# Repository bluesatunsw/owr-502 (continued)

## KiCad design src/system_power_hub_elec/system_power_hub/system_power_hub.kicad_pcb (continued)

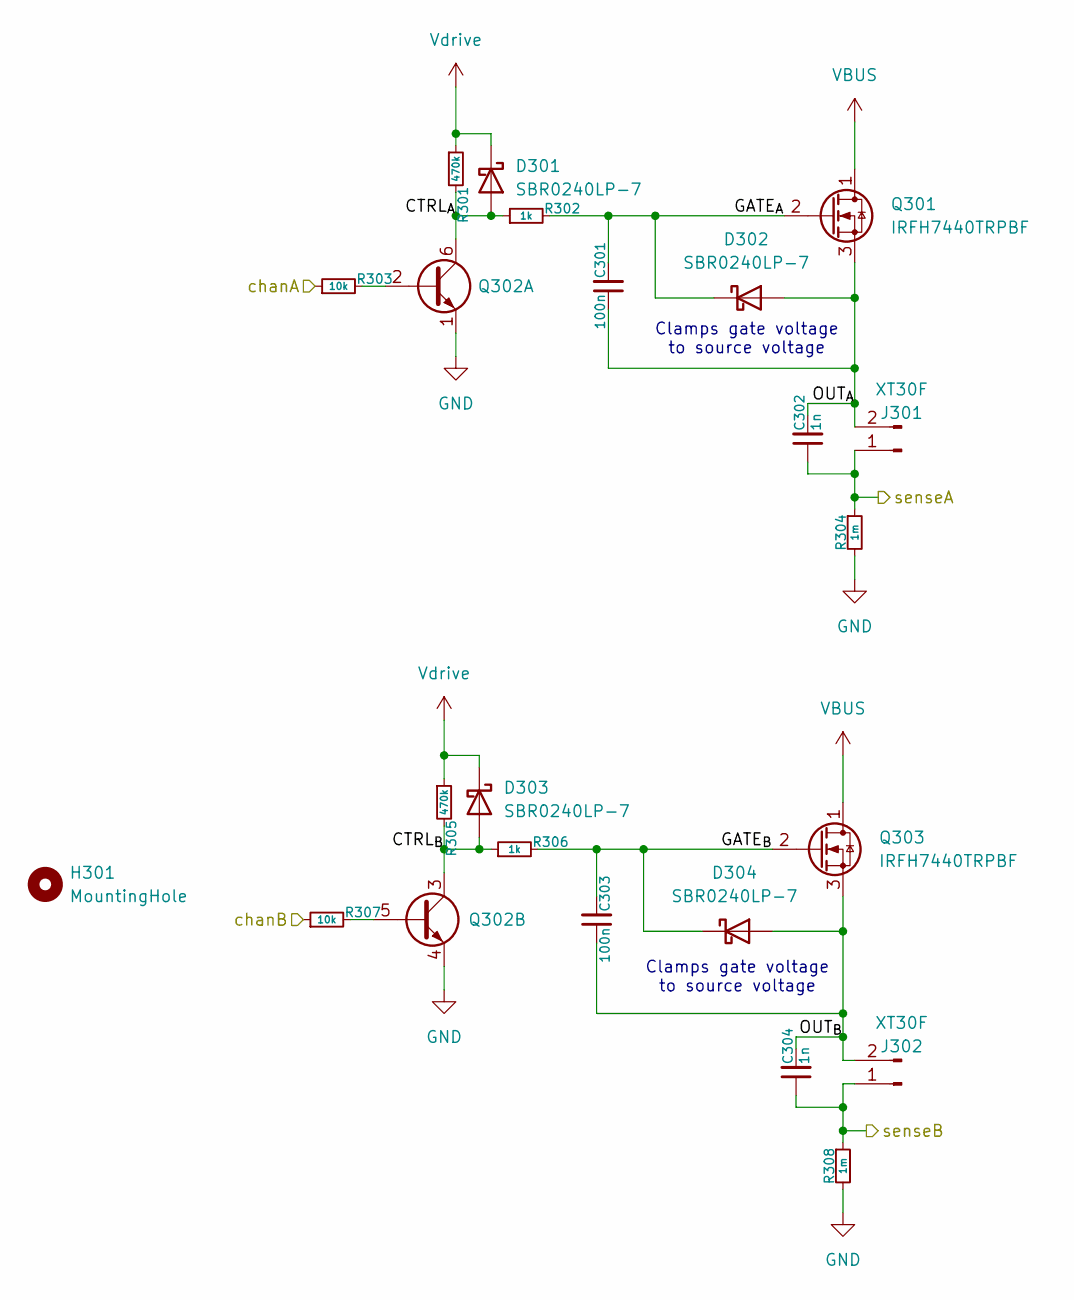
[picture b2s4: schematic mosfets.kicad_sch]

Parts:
C301, C303: 100n; C_0402_1005Metric
C302, C304: 1n; C_0402_1005Metric
D301, D302, D303, D304: SBR0240LP-7; D_SOD-882
H301: MountingHole; M2.5_Internal
J301, J302: XT30F; AMASS_XT30PW-F_1x02_P2.50mm_Horizontal
Q301, Q303: IRFH7440TRPBF; PQFN_5x6mm_E_DGS
Q302: Q_Dual_NPN_NPN_E1B1C2E2B2C1; SOT-363
R301, R305: 470k; R_0402_1005Metric
R302, R306: 1k; R_0402_1005Metric
R303, R307: 10k; R_0402_1005Metric
R304, R308: 1m; R_2512_6332Metric

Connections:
/Analog Stuff/Mosfets 1/CTRL_{A}: D301.2 (A), Q302.6 (C1), R301.2, R302.1
/Analog Stuff/Mosfets 1/CTRL_{B}: D303.2 (A), Q302.3 (C2), R305.2, R306.1
/Analog Stuff/Mosfets 1/GATE_{A}: C301.2, D302.1 (K), Q301.2 (G), R302.2
/Analog Stuff/Mosfets 1/GATE_{B}: C303.2, D304.1 (K), Q303.2 (G), R306.2
/Analog Stuff/Mosfets 1/OUT_{A}: C301.1, C302.2, D302.2 (A), J301.2, Q301.3 (S)
/Analog Stuff/Mosfets 1/OUT_{B}: C303.1, C304.2, D304.2 (A), J302.2, Q303.3 (S)
/Analog Stuff/vsense_p2: C302.1, J301.1, R304.1; also elsewhere on the board
/Analog Stuff/vsense_p3: C304.1, J302.1, R308.1; also elsewhere on the board
/Analog Stuff/~chan2: R303.1; also elsewhere on the board
/Analog Stuff/~chan3: R307.1; also elsewhere on the board
GND: Q302.1 (E1), Q302.4 (E2), R304.2, R308.2; also elsewhere on the board
unnamed: Q302.2 (B1), R303.2
unnamed: Q302.5 (B2), R307.2
VBUS: Q301.1 (D), Q303.1 (D); also elsewhere on the board
Vdrive: D301.1 (K), D303.1 (K), R301.1, R305.1; also elsewhere on the board

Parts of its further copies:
C401, C403, C501, C503, C601, C603: 100n; C_0402_1005Metric
C402, C404, C502, C504, C602, C604: 1n; C_0402_1005Metric
D401, D402, D403, D404, D501, D502, D503, D504, D601, D602, D603, D604: SBR0240LP-7; D_SOD-882
H401, H501, H601: MountingHole; M2.5_Internal
J401, J402, J501, J502, J601, J602: XT30F; AMASS_XT30PW-F_1x02_P2.50mm_Horizontal
Q401, Q403, Q501, Q503, Q601, Q603: IRFH7440TRPBF; PQFN_5x6mm_E_DGS
Q402, Q502, Q602: Q_Dual_NPN_NPN_E1B1C2E2B2C1; SOT-363
R401, R405, R501, R505, R601, R605: 470k; R_0402_1005Metric
R402, R406, R502, R506, R602, R606: 1k; R_0402_1005Metric
R403, R407, R503, R507, R603, R607: 10k; R_0402_1005Metric
R404, R408, R504, R508, R604, R608: 1m; R_2512_6332Metric

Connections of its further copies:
/Analog Stuff/Mosfets 2/CTRL_{A}: D401.2 (A), Q402.6 (C1), R401.2, R402.1
/Analog Stuff/Mosfets 2/CTRL_{B}: D403.2 (A), Q402.3 (C2), R405.2, R406.1
/Analog Stuff/Mosfets 2/GATE_{A}: C401.2, D402.1 (K), Q401.2 (G), R402.2
/Analog Stuff/Mosfets 2/GATE_{B}: C403.2, D404.1 (K), Q403.2 (G), R406.2
/Analog Stuff/Mosfets 2/OUT_{A}: C401.1, C402.2, D402.2 (A), J401.2, Q401.3 (S)
/Analog Stuff/Mosfets 2/OUT_{B}: C403.1, C404.2, D404.2 (A), J402.2, Q403.3 (S)
/Analog Stuff/Mosfets 3/CTRL_{A}: D501.2 (A), Q502.6 (C1), R501.2, R502.1
/Analog Stuff/Mosfets 3/CTRL_{B}: D503.2 (A), Q502.3 (C2), R505.2, R506.1
/Analog Stuff/Mosfets 3/GATE_{A}: C501.2, D502.1 (K), Q501.2 (G), R502.2
/Analog Stuff/Mosfets 3/GATE_{B}: C503.2, D504.1 (K), Q503.2 (G), R506.2
/Analog Stuff/Mosfets 3/OUT_{A}: C501.1, C502.2, D502.2 (A), J501.2, Q501.3 (S)
/Analog Stuff/Mosfets 3/OUT_{B}: C503.1, C504.2, D504.2 (A), J502.2, Q503.3 (S)
/Analog Stuff/Mosfets 4/CTRL_{A}: D601.2 (A), Q602.6 (C1), R601.2, R602.1
/Analog Stuff/Mosfets 4/CTRL_{B}: D603.2 (A), Q602.3 (C2), R605.2, R606.1
/Analog Stuff/Mosfets 4/GATE_{A}: C601.2, D602.1 (K), Q601.2 (G), R602.2
/Analog Stuff/Mosfets 4/GATE_{B}: C603.2, D604.1 (K), Q603.2 (G), R606.2
/Analog Stuff/Mosfets 4/OUT_{A}: C601.1, C602.2, D602.2 (A), J601.2, Q601.3 (S)
/Analog Stuff/Mosfets 4/OUT_{B}: C603.1, C604.2, D604.2 (A), J602.2, Q603.3 (S)
/Analog Stuff/vsense_p0: C402.1, J401.1, R404.1; also elsewhere on the board
/Analog Stuff/vsense_p1: C404.1, J402.1, R408.1; also elsewhere on the board
/Analog Stuff/vsense_p4: C502.1, J501.1, R504.1; also elsewhere on the board
/Analog Stuff/vsense_p5: C504.1, J502.1, R508.1; also elsewhere on the board
/Analog Stuff/vsense_p6: C602.1, J601.1, R604.1; also elsewhere on the board
/Analog Stuff/vsense_p7: C604.1, J602.1, R608.1; also elsewhere on the board
/Analog Stuff/~chan0: R403.1; also elsewhere on the board
/Analog Stuff/~chan1: R407.1; also elsewhere on the board
/Analog Stuff/~chan4: R503.1; also elsewhere on the board
/Analog Stuff/~chan5: R507.1; also elsewhere on the board
/Analog Stuff/~chan6: R603.1; also elsewhere on the board
/Analog Stuff/~chan7: R607.1; also elsewhere on the board
GND: Q402.1 (E1), Q402.4 (E2), Q502.1 (E1), Q502.4 (E2), Q602.1 (E1), Q602.4 (E2), R404.2, R408.2, R504.2, R508.2, R604.2, R608.2; also elsewhere on the board
unnamed: Q402.2 (B1), R403.2
unnamed: Q402.5 (B2), R407.2
unnamed: Q502.2 (B1), R503.2
unnamed: Q502.5 (B2), R507.2
unnamed: Q602.2 (B1), R603.2
unnamed: Q602.5 (B2), R607.2
VBUS: Q401.1 (D), Q403.1 (D), Q501.1 (D), Q503.1 (D), Q601.1 (D), Q603.1 (D); also elsewhere on the board
Vdrive: D401.1 (K), D403.1 (K), D501.1 (K), D503.1 (K), D601.1 (K), D603.1 (K), R401.1, R405.1, R501.1, R505.1, R601.1, R605.1; also elsewhere on the board

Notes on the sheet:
Clamps gate voltage to source voltage

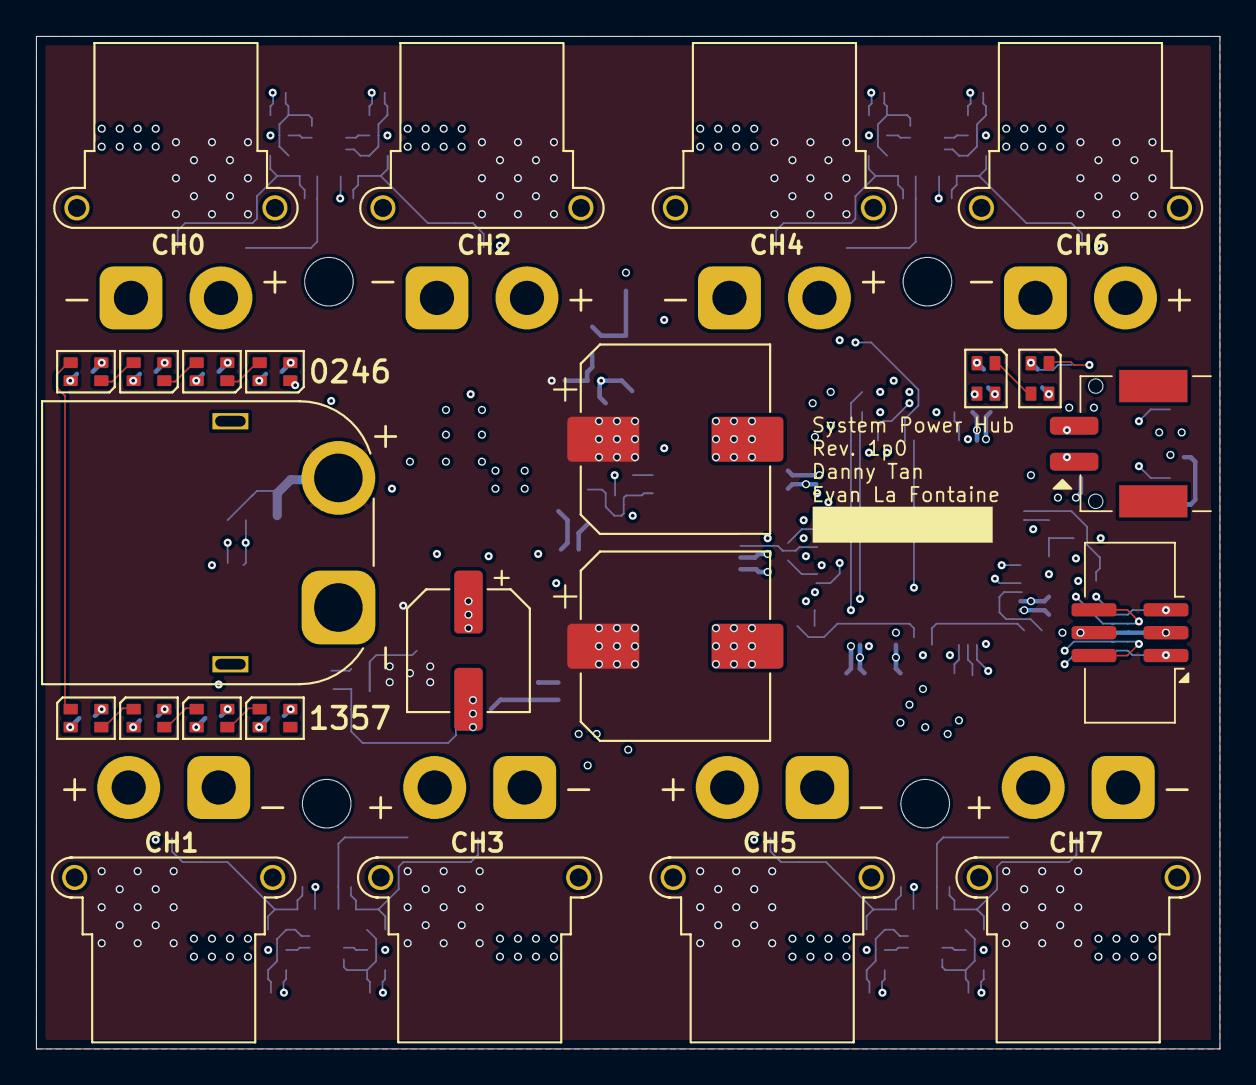
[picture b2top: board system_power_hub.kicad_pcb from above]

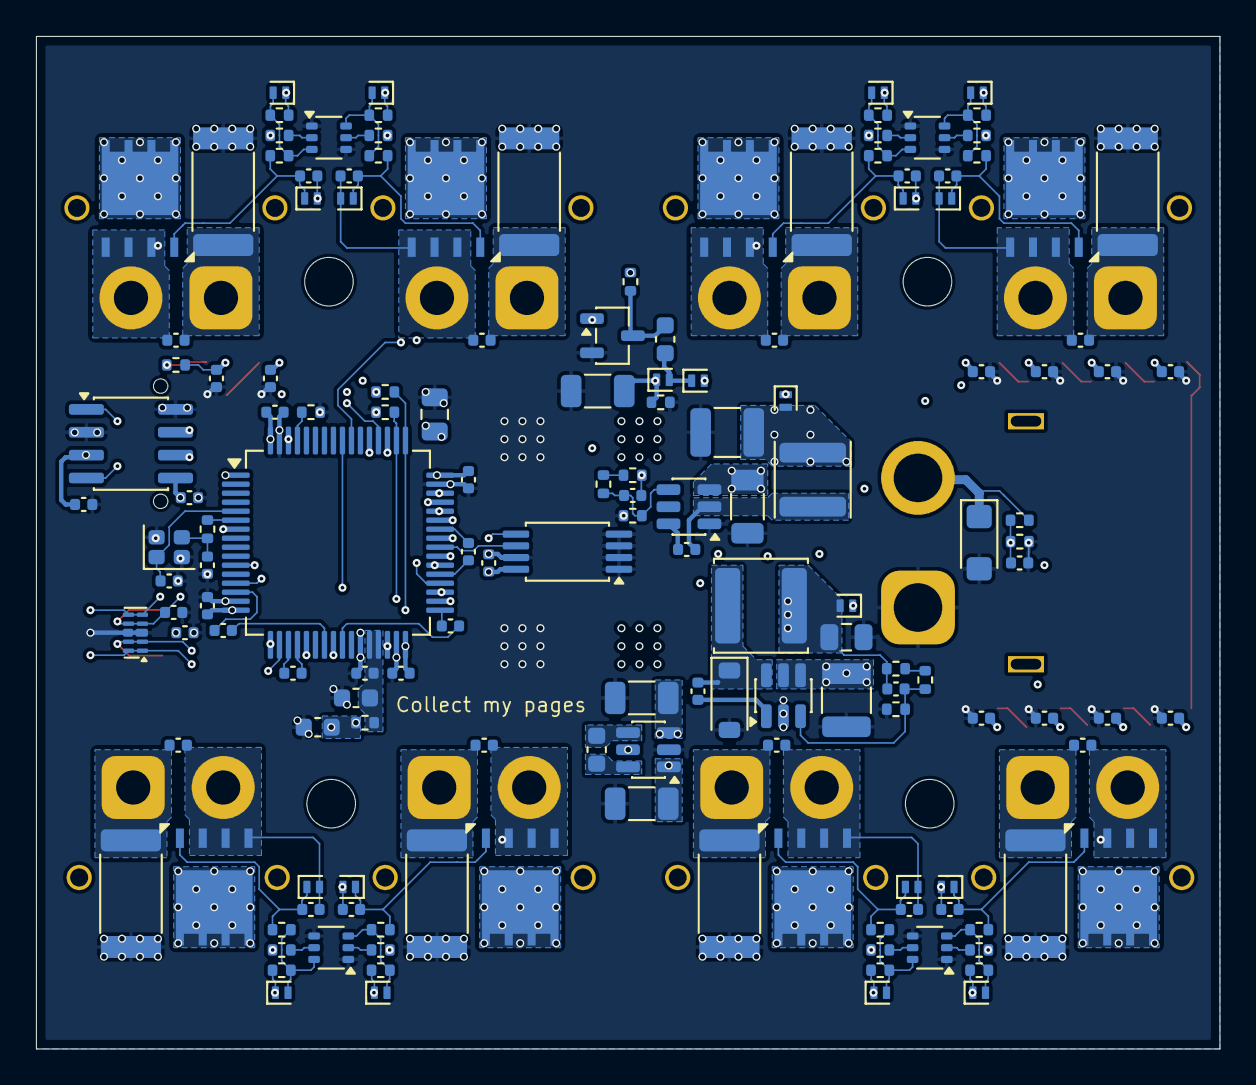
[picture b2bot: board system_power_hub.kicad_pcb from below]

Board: 6 copper layers, 65.8 x 56.2 mm, 180 parts (152 on the bottom side), 101 nets.

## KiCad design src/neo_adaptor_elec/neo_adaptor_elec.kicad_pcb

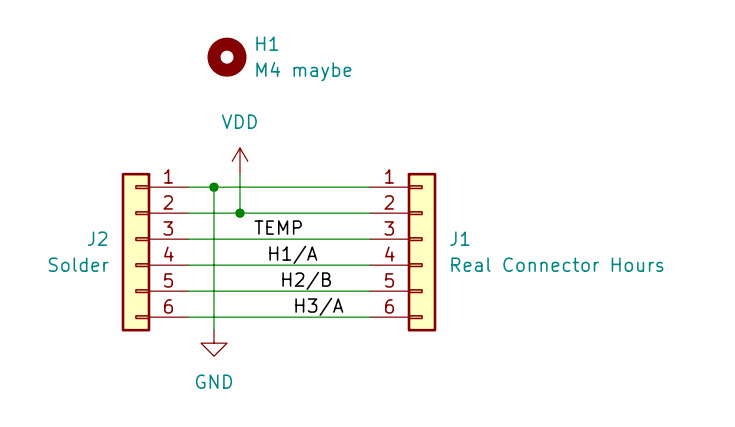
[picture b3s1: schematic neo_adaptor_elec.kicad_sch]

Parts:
H1: M4 maybe; MountingHole_4.3mm_M4
J1: Real Connector Hours; SM06B-PASS
J2: Solder; SolderWire-0.25sqmm_1x06_P4.2mm_D0.65mm_OD1.7mm

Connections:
/H1/A: J1.4, J2.4
/H2/B: J1.5, J2.5
/H3/A: J1.6, J2.6
/TEMP: J1.3, J2.3
GND: J1.1, J2.1
VDD: J1.2, J2.2

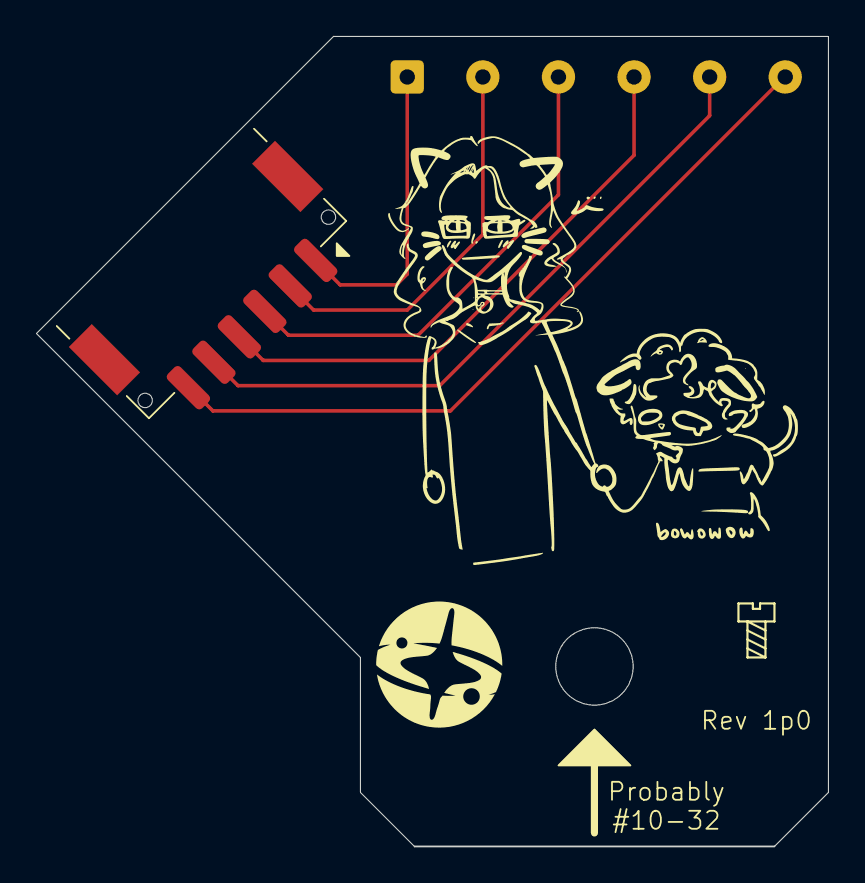
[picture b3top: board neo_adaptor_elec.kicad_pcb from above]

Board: 2 copper layers, 44.0 x 45.0 mm, 3 parts (0 on the bottom side), 6 nets.

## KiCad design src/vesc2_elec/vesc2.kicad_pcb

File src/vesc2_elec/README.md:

# NOTES FROM CREATOR

### Datasheets:
- DRV8301 Gate Driver https://www.ti.com/lit/ds/symlink/drv8301.pdf

## TODO
- Replace VESC volder with this one
- Add board temp sens to it (PA3 rn)

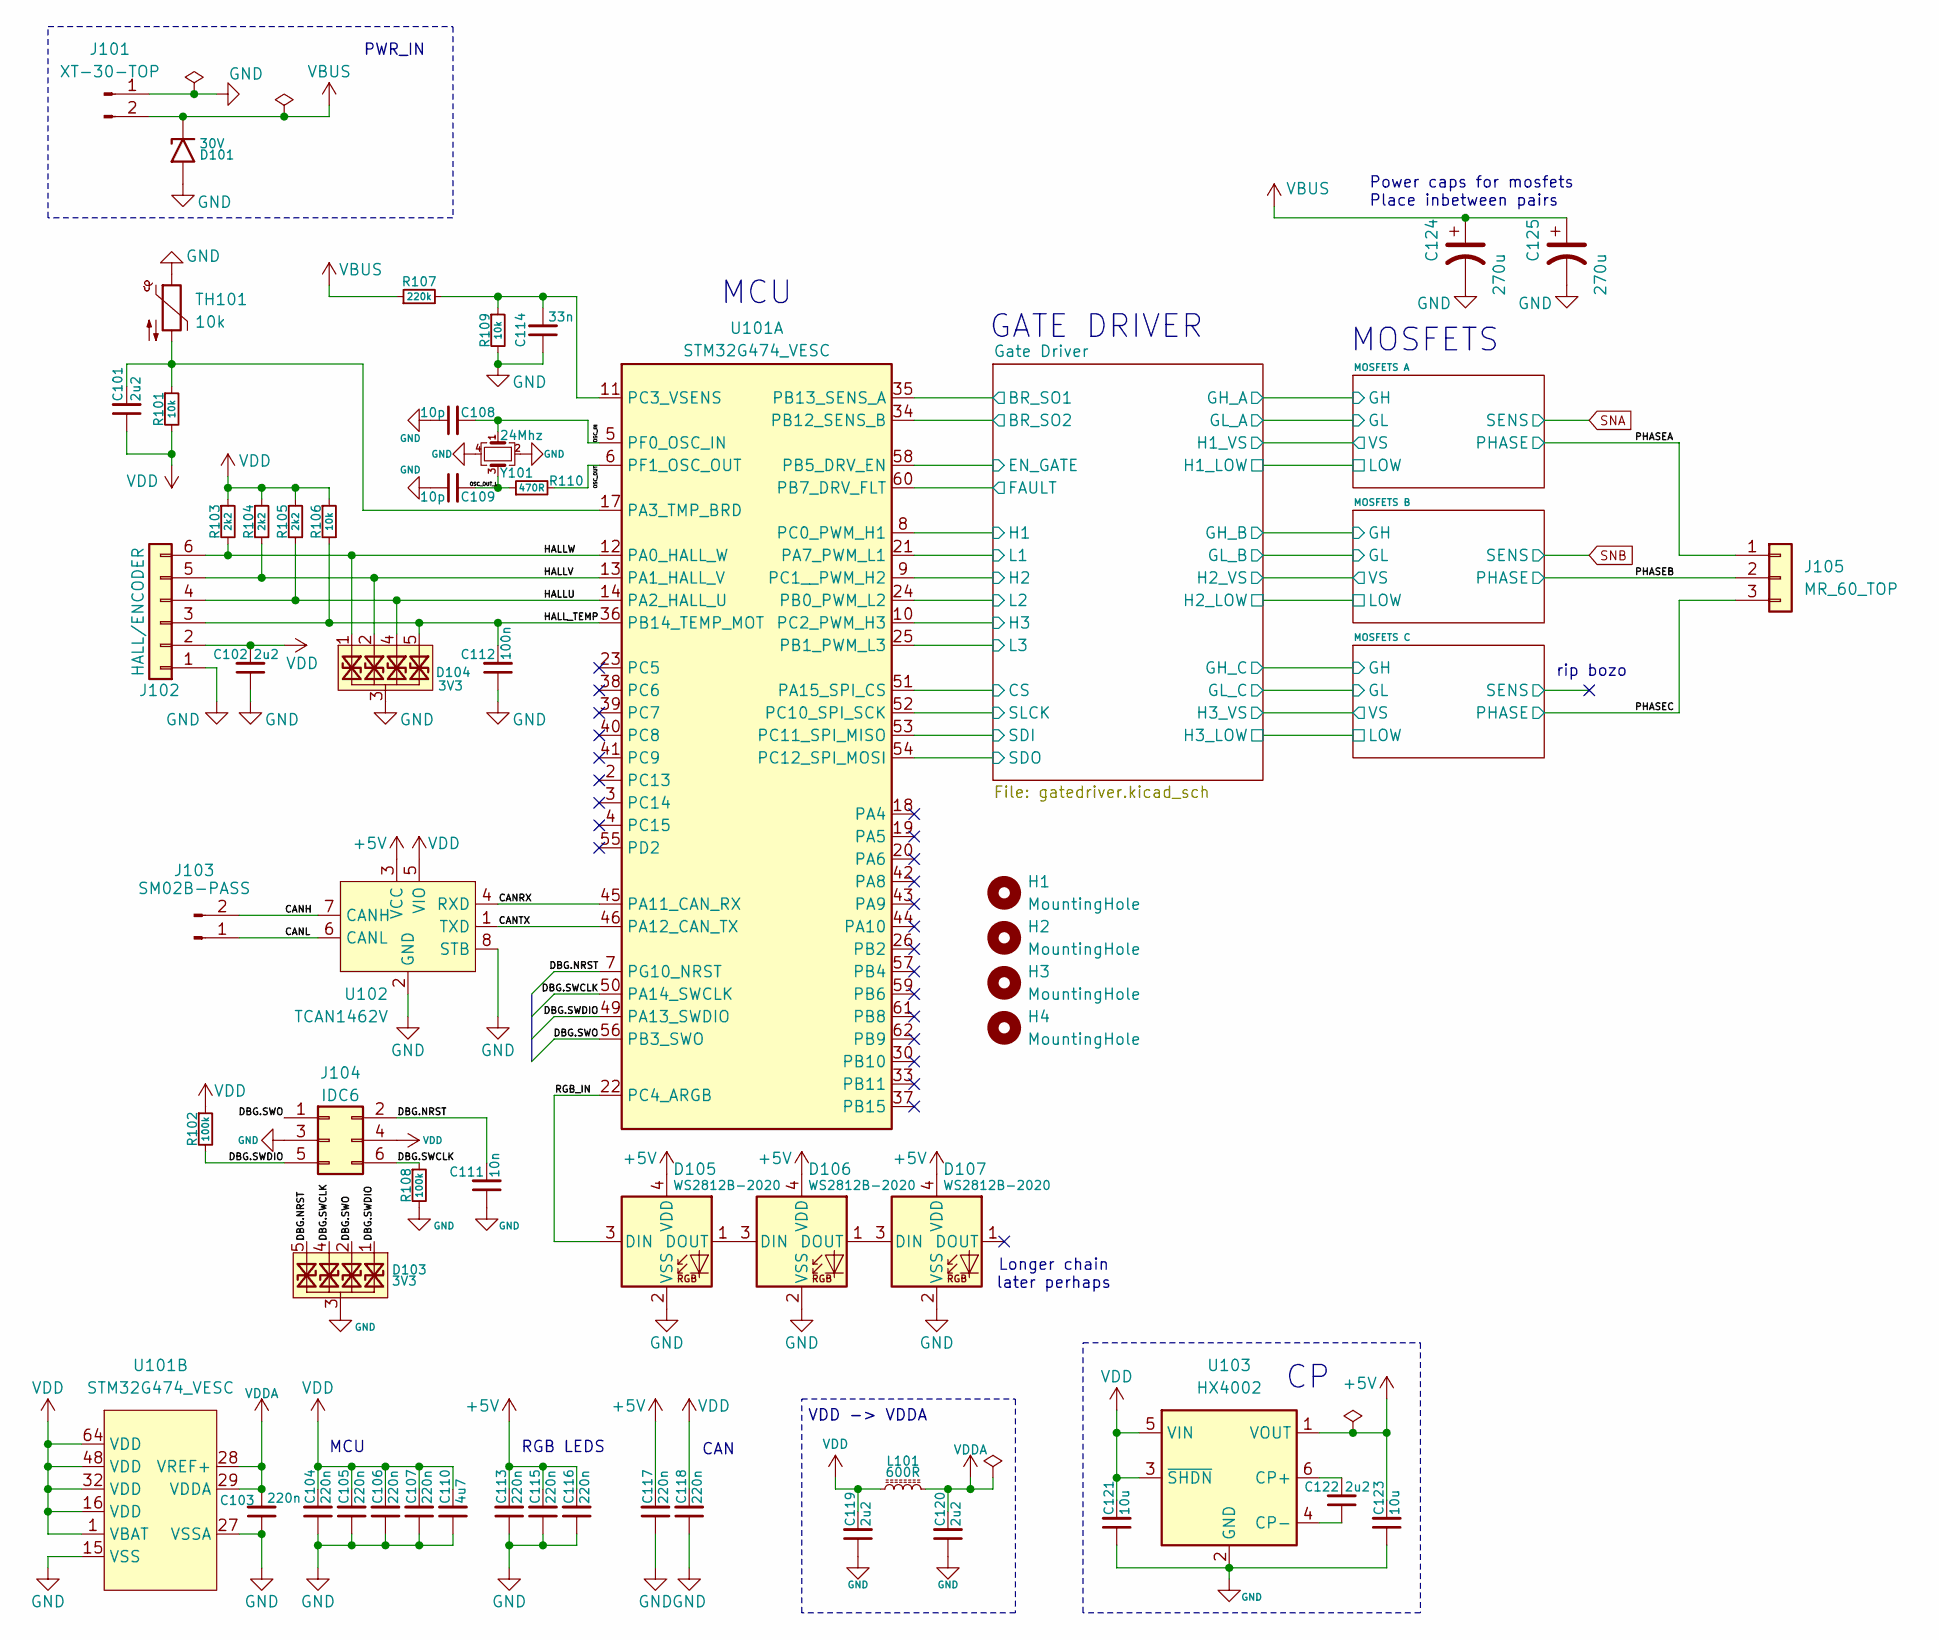
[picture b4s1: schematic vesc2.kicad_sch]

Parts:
C101, C102, C119, C120, C122: 2u2; C_0603_1608Metric
C103, C104, C105, C106, C107, C113, C115, C116, C117, C118: 220n; C_0402_1005Metric
C108, C109: 10p; C_0402_1005Metric
C110: 4u7; C_0805_2012Metric
C111: 10n; C_0402_1005Metric
C112: 100n; C_0402_1005Metric
C114: 33n; C_0402_1005Metric
C121, C123: 10u; C_1206_3216Metric
C124, C125: 270u; CP_Elec_10x10
D101: 30V; D_SMF
D103, D104: 3V3; Diodes_UDFN-10_1.0x2.5mm_P0.5mm
D105, D106, D107: WS2812B-2020
H1, H2, H3, H4: MountingHole; M2.5_Edge
J101: XT-30-TOP; XT30PW-M_1x02_P2.50mm_Top_mount
J102: HALL/ENCODER; BM06B-PASS
J103: SM02B-PASS; BM02B-PASS
J104: IDC6
J105: MR_60_TOP; MR60-F-TopMount
L101: 600R; R_0402_1005Metric
R101, R106, R109: 10k; R_0402_1005Metric
R102, R108: 100k; R_0402_1005Metric
R103, R104, R105: 2k2; R_0402_1005Metric
R107: 220k; R_0402_1005Metric
R110: 470R; R_0402_1005Metric
TH101: 10k; R_0402_1005Metric
U101: STM32G474_VESC; LQFP-64-0.5
U102: TCAN1462V; SOIC-8_3.9x4.9mm_P1.27mm
U103: HX4002; SOT-23-6
Y101: 24Mhz; Crystal_SMD_2016-4Pin_2.0x1.6mm

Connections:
+5V: C113.2, C115.2, C116.2, C117.2, C123.2, D105.4 (VDD), D106.4 (VDD), D107.4 (VDD), U102.3 (VCC), U103.1 (VOUT)
/CANH: J103.2, U102.7 (CANH); also elsewhere on the board
/CANL: J103.1, U102.6 (CANL); also elsewhere on the board
/CANRX: U101.45 (PA11_CAN_RX), U102.4 (RXD)
/CANTX: U101.46 (PA12_CAN_TX), U102.1 (TXD)
/DBG.NRST: C111.2, D103.5, D103.6, J104.2, U101.7 (PG10_NRST)
/DBG.SWCLK: D103.4, D103.7, J104.6, R108.1, U101.50 (PA14_SWCLK)
/DBG.SWDIO: D103.1, D103.10, J104.5, R102.2, U101.49 (PA13_SWDIO)
/DBG.SWO: D103.2, D103.9, J104.1, U101.56 (PB3_SWO)
/Gate Driver/BR_SO1: U101.35 (PB13_SENS_A); also elsewhere on the board
/Gate Driver/BR_SO2: U101.34 (PB12_SENS_B); also elsewhere on the board
/Gate Driver/CS: U101.51 (PA15_SPI_CS); also elsewhere on the board
/Gate Driver/EN_GATE: U101.58 (PB5_DRV_EN); also elsewhere on the board
/Gate Driver/FAULT: U101.60 (PB7_DRV_FLT); also elsewhere on the board
/Gate Driver/H1: U101.8 (PC0_PWM_H1); also elsewhere on the board
/Gate Driver/H2: U101.9 (PC1__PWM_H2); also elsewhere on the board
/Gate Driver/H3: U101.10 (PC2_PWM_H3); also elsewhere on the board
/Gate Driver/L1: U101.21 (PA7_PWM_L1); also elsewhere on the board
/Gate Driver/L2: U101.24 (PB0_PWM_L2); also elsewhere on the board
/Gate Driver/L3: U101.25 (PB1_PWM_L3); also elsewhere on the board
/Gate Driver/SDI: U101.53 (PC11_SPI_MISO); also elsewhere on the board
/Gate Driver/SDO: U101.54 (PC12_SPI_MOSI); also elsewhere on the board
/Gate Driver/SLCK: U101.52 (PC10_SPI_SCK); also elsewhere on the board
/HALLU: D104.4, D104.7, J102.4, R105.2, U101.14 (PA2_HALL_U)
/HALLV: D104.2, D104.9, J102.5, R104.2, U101.13 (PA1_HALL_V)
/HALLW: D104.1, D104.10, J102.6, R103.2, U101.12 (PA0_HALL_W)
/HALL_TEMP: C112.2, D104.5, D104.6, J102.3, R106.2, U101.36 (PB14_TEMP_MOT)
/OSC_IN: C108.2, U101.5 (PF0_OSC_IN), Y101.1
/OSC_OUT: R110.2, U101.6 (PF1_OSC_OUT)
/OSC_OUT_L: C109.2, R110.1, Y101.3
/PHASEA: J105.1; also elsewhere on the board
/PHASEB: J105.2; also elsewhere on the board
/PHASEC: J105.3; also elsewhere on the board
/RGB_IN: D105.3 (DIN), U101.22 (PC4_ARGB)
GND: C102.1, C103.1, C104.1, C105.1, C106.1, C107.1, C108.1, C109.1, C110.1, C111.1, C112.1, C113.1, C114.1, C115.1, C116.1, C117.1, C118.1, C119.1, C120.1, C121.1, C123.1, C124.2, C125.2, D101.2 (A2), D103.3, D103.8, D104.3, D104.8, D105.2 (VSS), D106.2 (VSS), D107.2 (VSS), J101.1, J102.1, J104.3, R108.2, R109.2, TH101.1, U101.15 (VSS), U101.27 (VSSA), U101.31 (VSS), U101.47 (VSS), U101.63 (VSS), U102.2 (GND), U102.8 (STB), U102.9 (EP), U103.2 (GND), Y101.2, Y101.4; also elsewhere on the board
unnamed: D105.1 (DOUT), D106.3 (DIN)
unnamed: D106.1 (DOUT), D107.3 (DIN)
unnamed: C101.2, R101.1, TH101.2, U101.17 (PA3_TMP_BRD)
unnamed: C114.2, R107.2, R109.1, U101.11 (PC3_VSENS)
unnamed: C122.2, U103.6 (CP+)
unnamed: C122.1, U103.4 (CP-)
VDD: C101.1, C102.2, C104.2, C105.2, C106.2, C107.2, C110.2, C118.2, C119.2, C121.2, J102.2, J104.4, L101.1, R101.2, R102.1, R103.1, R104.1, R105.1, R106.1, U101.1 (VBAT), U101.16 (VDD), U101.32 (VDD), U101.48 (VDD), U101.64 (VDD), U102.5 (VIO), U103.3 (~SHDN), U103.5 (VIN); also elsewhere on the board
VDDA: C103.2, C120.2, L101.2, U101.28 (VREF+), U101.29 (VDDA)

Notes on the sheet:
RGB LEDS
Power caps for mosfets Place inbetween pairs
rip bozo
GATE DRIVER
MCU
CAN
VDD -> VDDA
MOSFETS
Longer chain later perhaps
PWR_IN

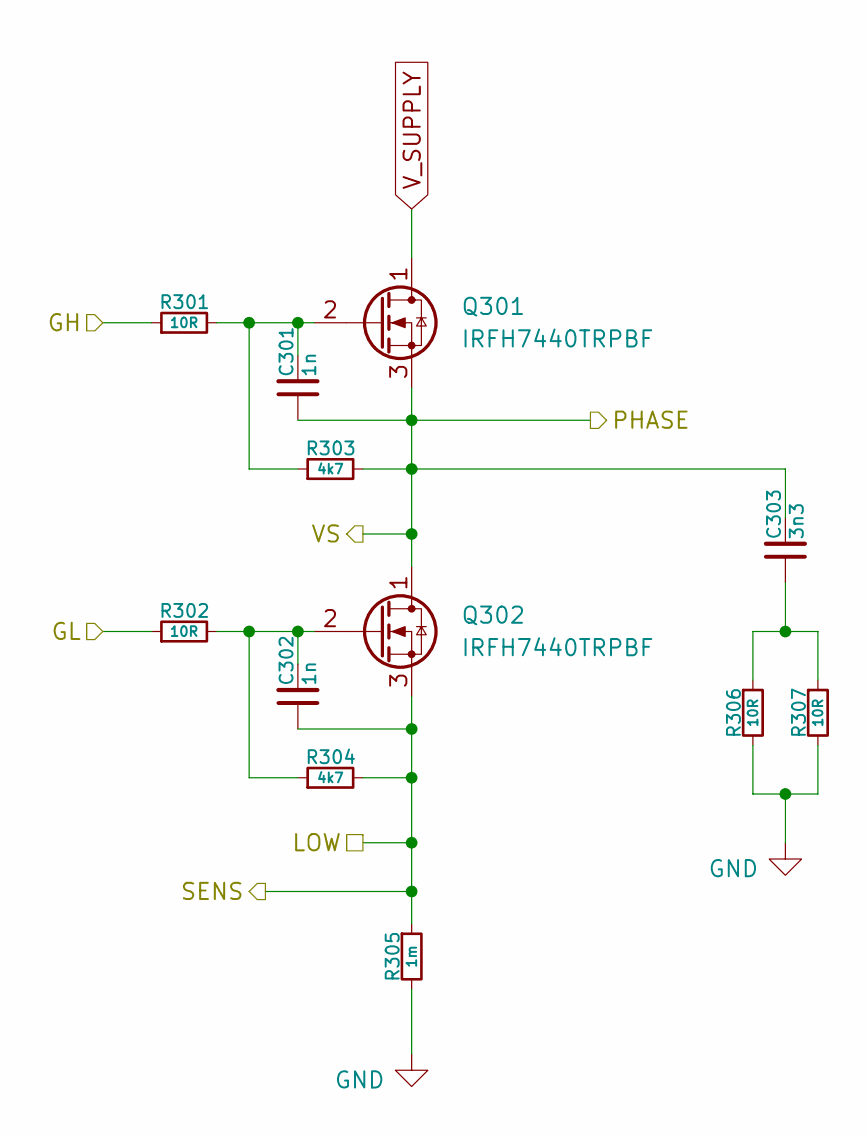
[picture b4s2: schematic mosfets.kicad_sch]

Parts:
C301, C302: 1n; C_0402_1005Metric
C303: 3n3; C_0402_1005Metric
Q301, Q302: IRFH7440TRPBF; PQFN_5x6mm_E_DGS
R301, R302, R306, R307: 10R; R_0402_1005Metric
R303, R304: 4k7; R_0402_1005Metric
R305: 1m; R_2512_6332Metric

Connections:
/Gate Driver/GH_A: R301.1; also elsewhere on the board
/Gate Driver/GL_A: R302.1; also elsewhere on the board
/PHASEA: C301.1, C303.2, Q301.3 (S), Q302.1 (D), R303.2; also elsewhere on the board
GND: R305.2, R306.2, R307.2; also elsewhere on the board
unnamed: C303.1, R306.1, R307.1
unnamed: C301.2, Q301.2 (G), R301.2, R303.1
unnamed: C302.2, Q302.2 (G), R302.2, R304.1
SNA: C302.1, Q302.3 (S), R304.2, R305.1; also elsewhere on the board

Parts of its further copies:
C401, C402, C501, C502: 1n; C_0402_1005Metric
C403, C503: 3n3; C_0402_1005Metric
Q401, Q402, Q501, Q502: IRFH7440TRPBF; PQFN_5x6mm_E_DGS
R401, R402, R406, R407, R501, R502, R506, R507: 10R; R_0402_1005Metric
R403, R404, R503, R504: 4k7; R_0402_1005Metric
R405, R505: 1m; R_2512_6332Metric

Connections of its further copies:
/Gate Driver/GH_B: R401.1; also elsewhere on the board
/Gate Driver/GH_C: R501.1; also elsewhere on the board
/Gate Driver/GL_B: R402.1; also elsewhere on the board
/Gate Driver/GL_C: R502.1; also elsewhere on the board
/Gate Driver/H3_LOW: C502.1, Q502.3 (S), R504.2, R505.1; also elsewhere on the board
/PHASEB: C401.1, C403.2, Q401.3 (S), Q402.1 (D), R403.2; also elsewhere on the board
/PHASEC: C501.1, C503.2, Q501.3 (S), Q502.1 (D), R503.2; also elsewhere on the board
GND: R405.2, R406.2, R407.2, R505.2, R506.2, R507.2; also elsewhere on the board
unnamed: C403.1, R406.1, R407.1
unnamed: C503.1, R506.1, R507.1
unnamed: C401.2, Q401.2 (G), R401.2, R403.1
unnamed: C402.2, Q402.2 (G), R402.2, R404.1
unnamed: C501.2, Q501.2 (G), R501.2, R503.1
unnamed: C502.2, Q502.2 (G), R502.2, R504.1
SNB: C402.1, Q402.3 (S), R404.2, R405.1; also elsewhere on the board

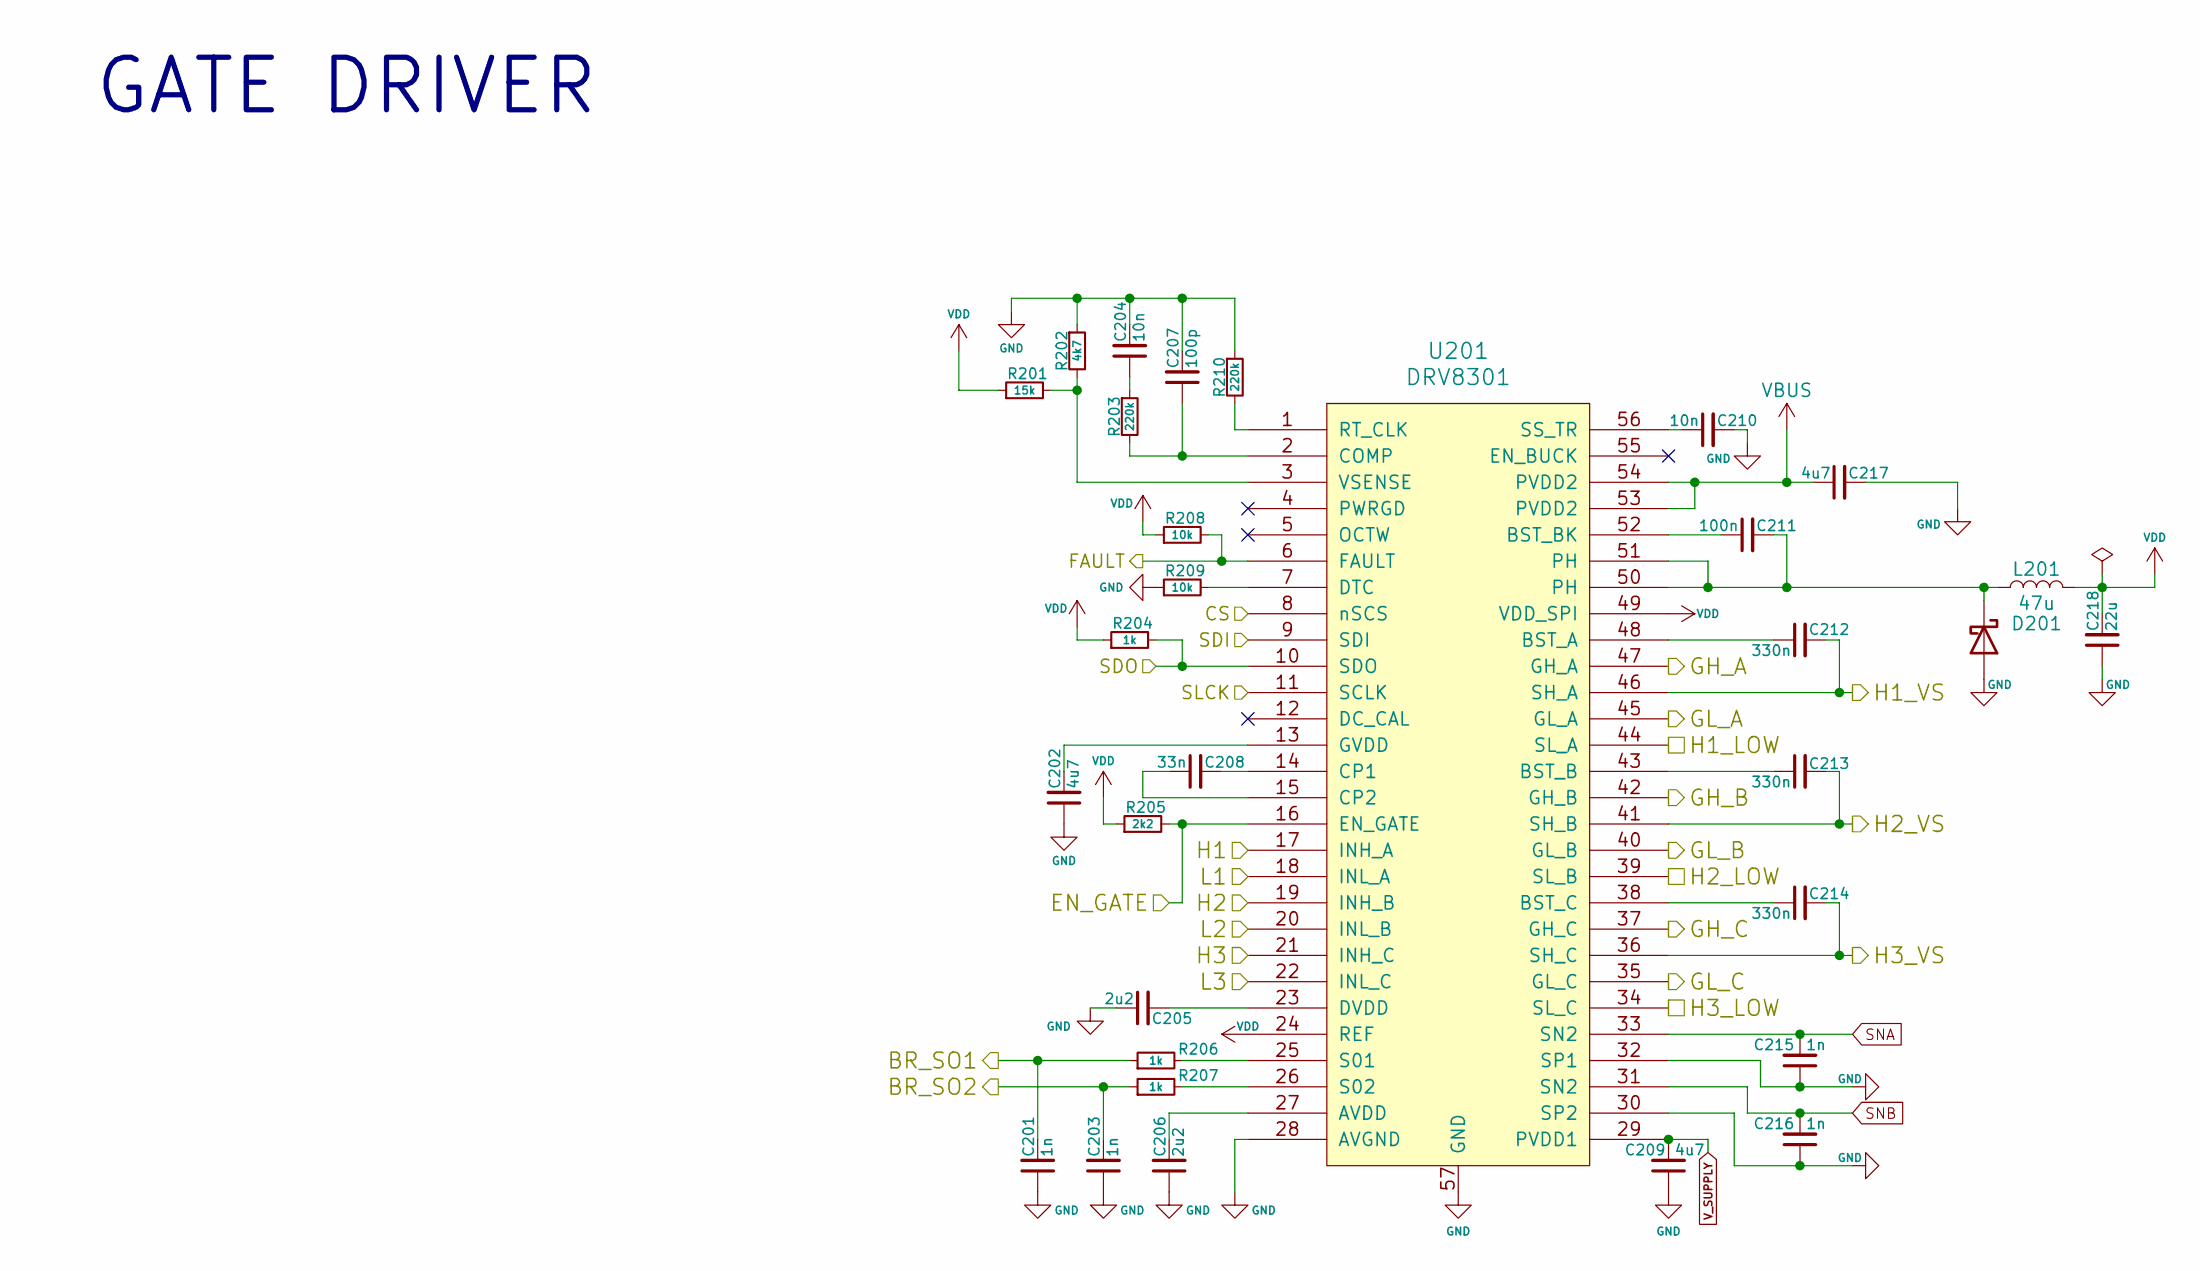
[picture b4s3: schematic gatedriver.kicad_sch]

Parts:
C201, C203, C215, C216: 1n; C_0402_1005Metric
C202: 4u7; C_1206_3216Metric
C204, C210: 10n; C_0402_1005Metric
C205, C206: 2u2; C_0603_1608Metric
C207: 100p; C_0402_1005Metric
C208: 33n; C_0603_1608Metric
C209, C217: 4u7; C_1210_3225Metric
C211: 100n; C_0603_1608Metric
C212, C213, C214: 330n; C_0603_1608Metric
C218: 22u; C_1210_3225Metric
D201: D_Schottky; D_SOD-123
L201: 47u; L_Changjiang_FXL0630
R201: 15k; R_0402_1005Metric
R202: 4k7; R_0402_1005Metric
R203, R210: 220k; R_0402_1005Metric
R204, R206, R207: 1k; R_0402_1005Metric
R205: 2k2; R_0402_1005Metric
R208, R209: 10k; R_0402_1005Metric
U201: DRV8301; HTSSOP-56_6.1x14-0.5-EP

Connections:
/Gate Driver/BR_SO1: C201.2, R206.1; also elsewhere on the board
/Gate Driver/BR_SO2: C203.2, R207.1; also elsewhere on the board
/Gate Driver/CS: U201.8 (nSCS); also elsewhere on the board
/Gate Driver/EN_GATE: R205.2, U201.16 (EN_GATE); also elsewhere on the board
/Gate Driver/FAULT: R208.2, U201.6 (FAULT); also elsewhere on the board
/Gate Driver/GH_A: U201.47 (GH_A); also elsewhere on the board
/Gate Driver/GH_B: U201.42 (GH_B); also elsewhere on the board
/Gate Driver/GH_C: U201.37 (GH_C); also elsewhere on the board
/Gate Driver/GL_A: U201.45 (GL_A); also elsewhere on the board
/Gate Driver/GL_B: U201.40 (GL_B); also elsewhere on the board
/Gate Driver/GL_C: U201.35 (GL_C); also elsewhere on the board
/Gate Driver/H1: U201.17 (INH_A); also elsewhere on the board
/Gate Driver/H2: U201.19 (INH_B); also elsewhere on the board
/Gate Driver/H3: U201.21 (INH_C); also elsewhere on the board
/Gate Driver/H3_LOW: U201.34 (SL_C); also elsewhere on the board
/Gate Driver/L1: U201.18 (INL_A); also elsewhere on the board
/Gate Driver/L2: U201.20 (INL_B); also elsewhere on the board
/Gate Driver/L3: U201.22 (INL_C); also elsewhere on the board
/Gate Driver/SDI: U201.9 (SDI); also elsewhere on the board
/Gate Driver/SDO: R204.2, U201.10 (SDO); also elsewhere on the board
/Gate Driver/SLCK: U201.11 (SCLK); also elsewhere on the board
/PHASEA: C212.2, U201.46 (SH_A); also elsewhere on the board
/PHASEB: C213.2, U201.41 (SH_B); also elsewhere on the board
/PHASEC: C214.2, U201.36 (SH_C); also elsewhere on the board
GND: C201.1, C202.1, C203.1, C204.2, C205.1, C206.1, C207.2, C209.1, C210.2, C215.1, C216.1, C217.2, C218.1, D201.2 (A), R202.1, R209.1, R210.1, U201.28 (AVGND), U201.30 (SP2), U201.32 (SP1), U201.57 (GND); also elsewhere on the board
unnamed: C204.1, R203.1
unnamed: C211.2, D201.1 (K), L201.1, U201.50 (PH), U201.51 (PH)
unnamed: C206.2, U201.27 (AVDD)
unnamed: C212.1, U201.48 (BST_A)
unnamed: C213.1, U201.43 (BST_B)
unnamed: C211.1, U201.52 (BST_BK)
unnamed: C214.1, U201.38 (BST_C)
unnamed: C207.1, R203.2, U201.2 (COMP)
unnamed: C208.2, U201.14 (CP1)
unnamed: C208.1, U201.15 (CP2)
unnamed: R209.2, U201.7 (DTC)
unnamed: C205.2, U201.23 (DVDD)
unnamed: C202.2, U201.13 (GVDD)
unnamed: R210.2, U201.1 (RT_CLK)
unnamed: R206.2, U201.25 (S01)
unnamed: R207.2, U201.26 (S02)
unnamed: C210.1, U201.56 (SS_TR)
unnamed: R201.2, R202.2, U201.3 (VSENSE)
SNA: C215.2, U201.33 (SN2), U201.44 (SL_A); also elsewhere on the board
SNB: C216.2, U201.31 (SN2), U201.39 (SL_B); also elsewhere on the board
VDD: C218.2, L201.2, R201.1, R204.1, R205.1, R208.1, U201.24 (REF), U201.49 (VDD_SPI); also elsewhere on the board

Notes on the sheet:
GATE DRIVER

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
